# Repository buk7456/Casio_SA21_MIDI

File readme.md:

## Casio SA-21 midi conversion
A simple project to transform an old Casio keyboard into a MIDI controller, based around the ATmega328P microcontroller and 
Arduino enviroment.

### Main features
- Octave shifting
- Key transpose
- Adjustable note velocity
- Support for 5 midi channels

### Requirements for PC connection  
- Serial to USB module if using a stand-alone ATmega328P.
- Hairless MIDI to Serial Bridge for MIDI communication.
- LoopMIDI for virtual MIDI port creation.

### Hardware and shematics

You will need to desolder the original chip that comes with the keyboard so that it does not interfere
with the microcontroller. In my case I simply cut its pins to the key and button matrices.

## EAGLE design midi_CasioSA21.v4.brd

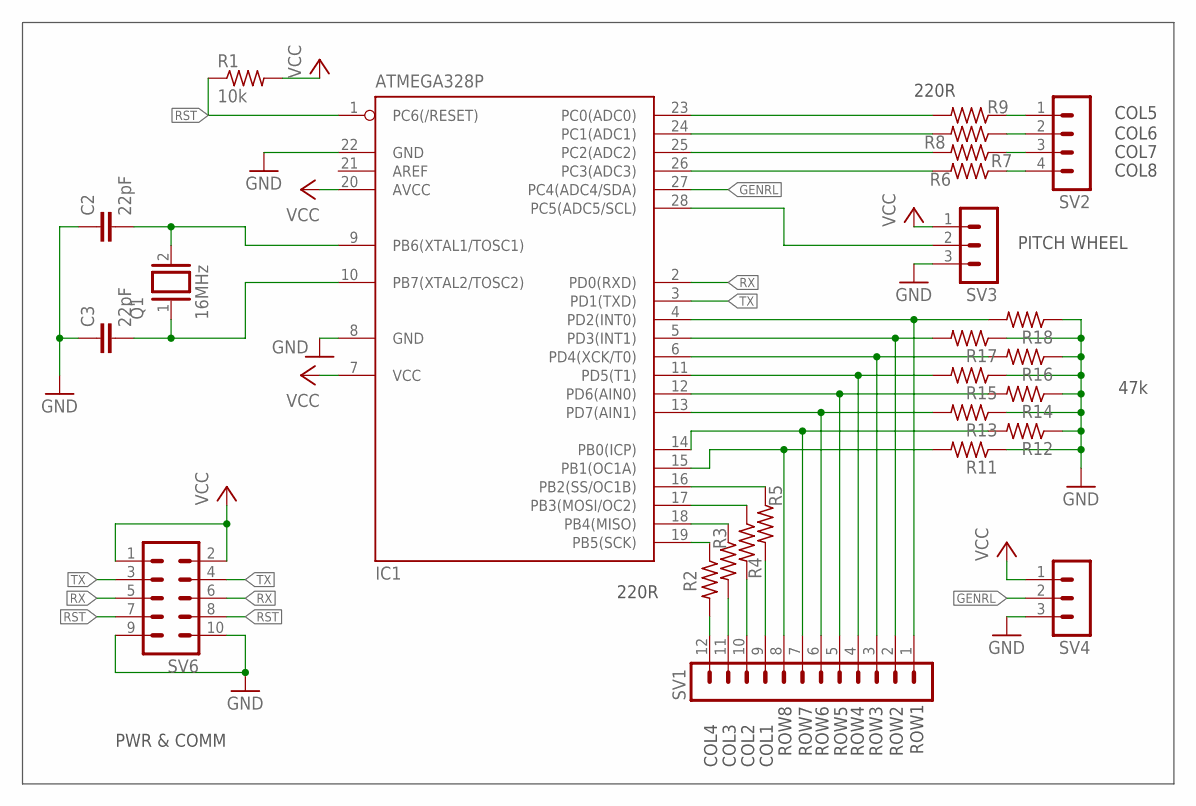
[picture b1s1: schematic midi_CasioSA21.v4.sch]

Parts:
C2, C3: 22pF; C025-025X050
IC1: ATMEGA328P; DIL28-3
Q1: 16MHz; QS
R1: 10k; 0204/7
R2, R6, R7, R8, R9, R11, R12, R13, R14, R15, R16, R17, R18: R-US_0204/5; 0204/5
R3, R4, R5: R-US_0204/2V; 0204V
SV1: MA12-1
SV2: MA04-1
SV3, SV4: MA03-1
SV6: MA05-2

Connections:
GENRL: IC1.27 (PC4(ADC4/SDA)), SV4.2
GND: C2.1, C3.1, IC1.8 (GND), IC1.22 (GND), R11.1, R12.1, R13.1, R14.1, R15.1, R16.1, R17.1, R18.1, SV3.3, SV4.3, SV6.9, SV6.10
unnamed: C2.2, IC1.9 (PB6(XTAL1/TOSC1)), Q1.2
unnamed: C3.2, IC1.10 (PB7(XTAL2/TOSC2)), Q1.1
unnamed: IC1.4 (PD2(INT0)), R18.2, SV1.1
unnamed: IC1.5 (PD3(INT1)), R17.2, SV1.2
unnamed: IC1.6 (PD4(XCK/T0)), R16.2, SV1.3
unnamed: R5.2, SV1.9
unnamed: IC1.11 (PD5(T1)), R15.2, SV1.4
unnamed: IC1.12 (PD6(AIN0)), R14.2, SV1.5
unnamed: IC1.13 (PD7(AIN1)), R13.2, SV1.6
unnamed: IC1.14 (PB0(ICP)), R12.2, SV1.7
unnamed: IC1.15 (PB1(OC1A)), R11.2, SV1.8
unnamed: IC1.19 (PB5(SCK)), R2.1
unnamed: IC1.18 (PB4(MISO)), R3.1
unnamed: IC1.17 (PB3(MOSI/OC2)), R4.1
unnamed: IC1.16 (PB2(SS/OC1B)), R5.1
unnamed: R4.2, SV1.10
unnamed: R3.2, SV1.11
unnamed: R2.2, SV1.12
unnamed: IC1.23 (PC0(ADC0)), R9.2
unnamed: IC1.24 (PC1(ADC1)), R8.2
unnamed: IC1.25 (PC2(ADC2)), R7.2
unnamed: IC1.26 (PC3(ADC3)), R6.2
unnamed: R9.1, SV2.1
unnamed: R8.1, SV2.2
unnamed: R7.1, SV2.3
unnamed: R6.1, SV2.4
PITCH_BEND: IC1.28 (PC5(ADC5/SCL)), SV3.2
RST: IC1.1 (PC6(/RESET)), R1.1, SV6.7, SV6.8
RX: IC1.2 (PD0(RXD)), SV6.5, SV6.6
TX: IC1.3 (PD1(TXD)), SV6.3, SV6.4
VCC: IC1.7 (VCC), IC1.20 (AVCC), R1.2, SV3.1, SV4.1, SV6.1, SV6.2

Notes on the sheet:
PITCH WHEEL
ROW1
ROW8
COL1
COL8
COL4
COL5
COL6
COL7
ROW2
ROW3
ROW4
ROW5
ROW6
COL2
COL3
ROW7
PWR & COMM
47k
220R

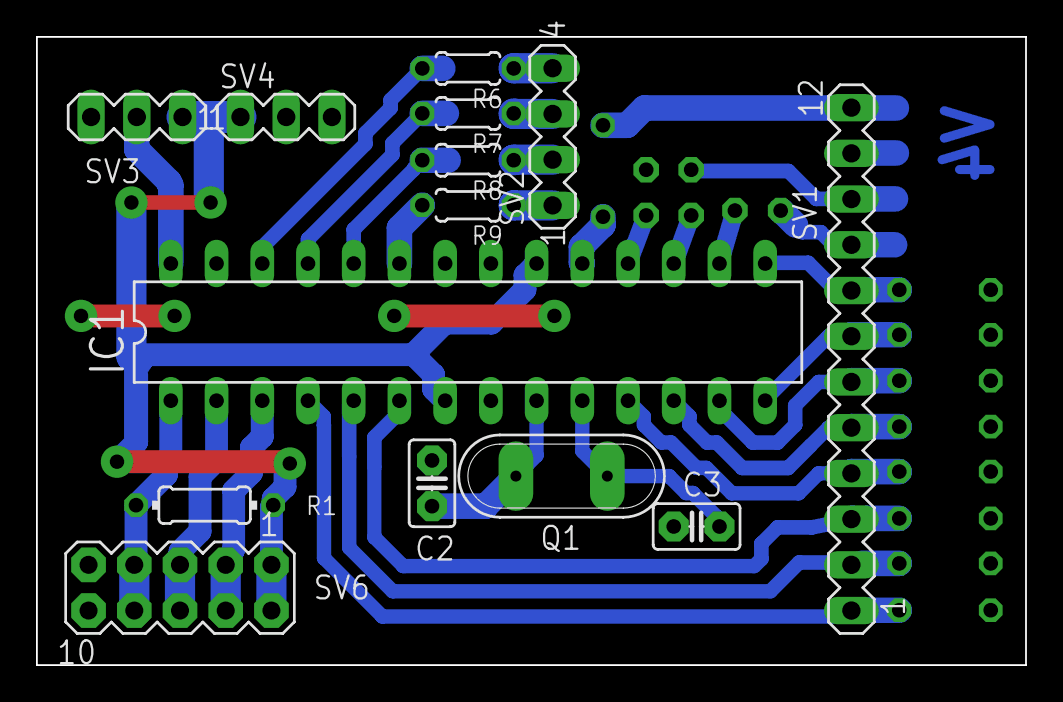
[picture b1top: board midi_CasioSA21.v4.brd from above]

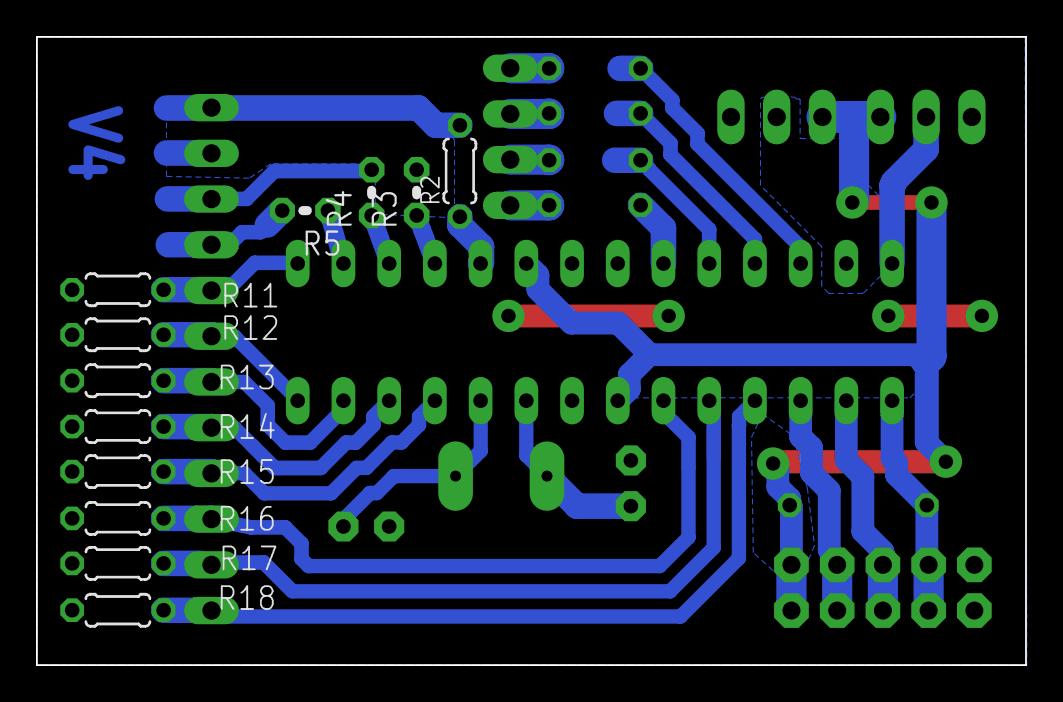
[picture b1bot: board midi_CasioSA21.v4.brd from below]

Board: 2 copper layers, 55.0 x 34.9 mm, 26 parts (12 on the bottom side), 33 nets.

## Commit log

2023-11-29 Removed unused variables
